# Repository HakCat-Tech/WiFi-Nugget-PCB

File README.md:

# WiFi Nugget PCB
This repository contains the PCB design files for the ESP8266 based WiFi Nugget.

### Change Log + Specs
**Beta-v1.0:**  
This design is a proof of concept for a slimmer, more easily manfacturable design based off surface mount components.   
- 0603 SMD components
- ESP12F based module
- SH1106 OLED Screen
- Minimal PCB art

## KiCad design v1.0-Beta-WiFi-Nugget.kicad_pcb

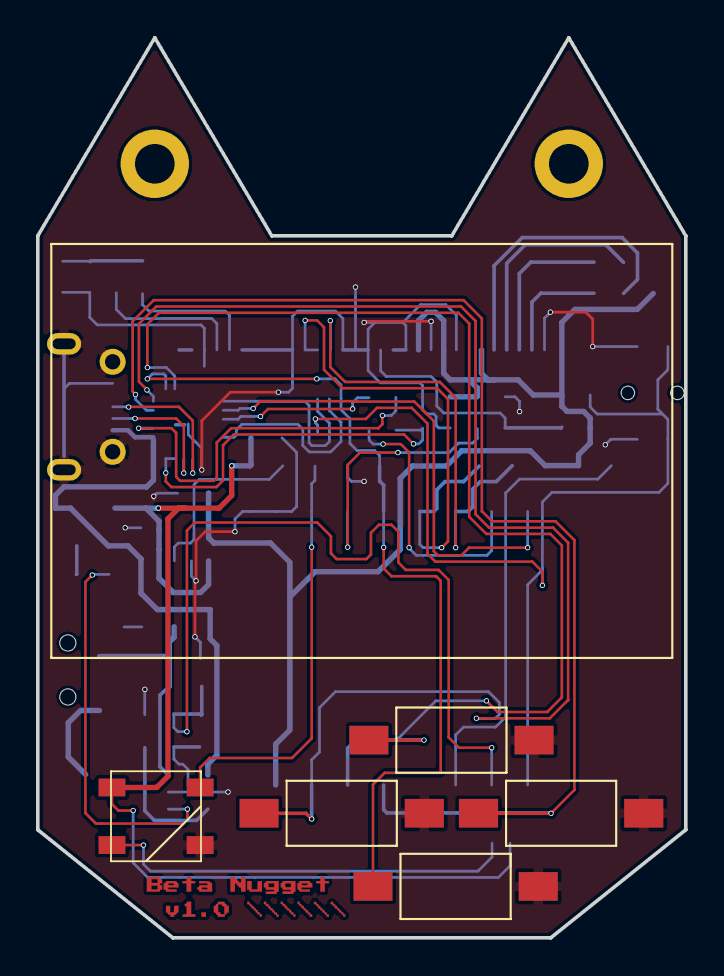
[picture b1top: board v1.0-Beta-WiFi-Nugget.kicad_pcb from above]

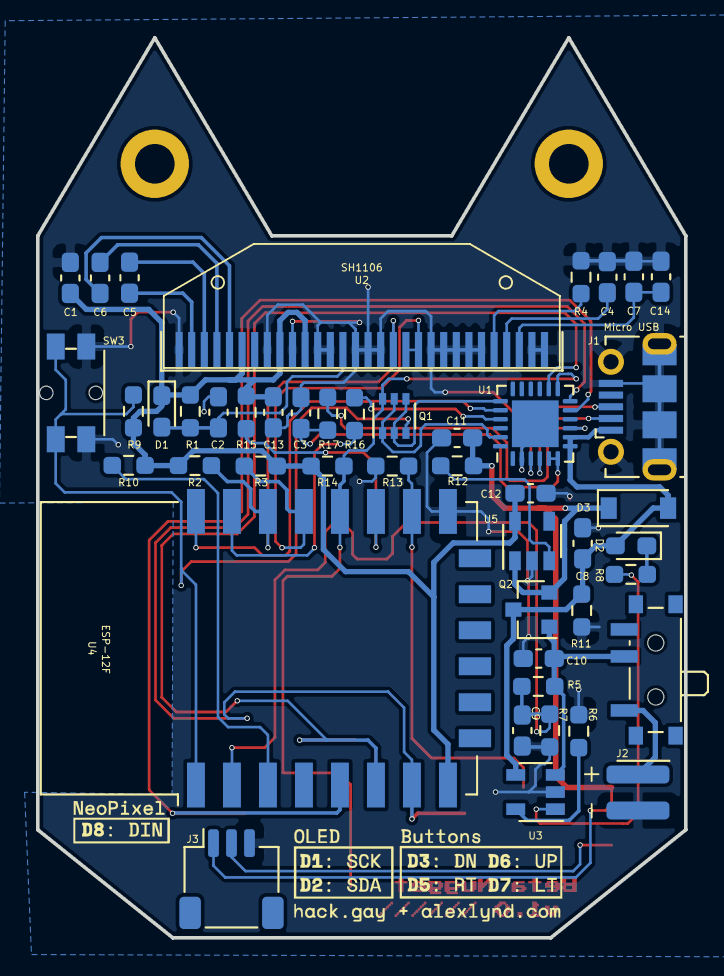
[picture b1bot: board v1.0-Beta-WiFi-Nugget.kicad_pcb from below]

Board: 2 copper layers, 36.0 x 50.0 mm, 52 parts (46 on the bottom side), 39 nets.

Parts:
C1, C3, C5, C6: 1 μF; C_0603_1608Metric_Pad1.08x0.95mm_HandSolder
C2: 10 μF; C_0603_1608Metric_Pad1.08x0.95mm_HandSolder
C4, C8, C10, C11, C12, C13: 4.7μF; C_0603_1608Metric_Pad1.08x0.95mm_HandSolder
C7, C14: C_Small; C_0603_1608Metric_Pad1.08x0.95mm_HandSolder
C9: 1μF; C_0603_1608Metric_Pad1.08x0.95mm_HandSolder
D1: SS14; LED_0603_1608Metric_Pad1.05x0.95mm_HandSolder
D2: RED; LED_0603_1608Metric_Pad1.05x0.95mm_HandSolder
D3: SS14; D_SOD-123
D4: WS2812B; LED_WS2812B_PLCC4_5.0x5.0mm_P3.2mm
J1: Micro USB; USB_Micro-B_Molex-105017-0001
J2: JST PH 2.0; JST_PH_S2B-PH-SM4-TB_1x02-1MP_P2.00mm_Horizontal
J3: JST_SH_SM03B-SRSS-TB_1x03-1MP_P1.00mm_Horizontal
Q1: UMH3N; SOT-363_SC-70-6
Q2: DMG3415; SOT-23
R1, R2, R3, R6, R13: 4.7K; R_0603_1608Metric_Pad0.98x0.95mm_HandSolder
R4: 560K; R_0603_1608Metric_Pad0.98x0.95mm_HandSolder
R5: 100K; R_0603_1608Metric_Pad0.98x0.95mm_HandSolder
R7: 27K; R_0603_1608Metric_Pad0.98x0.95mm_HandSolder
R8: 5K; R_0603_1608Metric_Pad0.98x0.95mm_HandSolder
R9, R10, R11, R12, R14, R15: 10K; R_0603_1608Metric_Pad0.98x0.95mm_HandSolder
R16: 1K; R_0603_1608Metric_Pad0.98x0.95mm_HandSolder
R17: R_Small_US; R_0603_1608Metric_Pad0.98x0.95mm_HandSolder
Ref**: Val**; Deluxe-Nugg-Board-Art
SW1: SPDT; SW_SPDT_PCM12
SW2: UP; SW_SPST_FSMSM
SW3: Reset; Panasonic_EVQPUM_EVQPUD
SW4: DOWN; SW_SPST_FSMSM
SW5: LEFT; SW_SPST_FSMSM
SW6: RIGHT; SW_SPST_FSMSM
U1: CP2102N-A01-GQFN24; QFN-24-1EP_4x4mm_P0.5mm_EP2.6x2.6mm
U2: SH1106; OLED-128O064D
U3: MCP73831-2-OT; SOT-23-5
U4: ESP-12F; ESP-12E
U5: AP2112K-3.3; SOT-23-5

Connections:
+3V3: C1.1, C12.1, C13.1, D1.1, R1.2, R2.1, R3.1, R9.1, R10.1, R14.1, R15.1, U2.6, U2.9, U2.11, U4.8, U5.5
+BATT: C10.1, Q2.1, R5.2, SW1.2, U3.3
A0: C9.2, R5.1, R7.2, U4.2
DOUT: D4.2, J3.2
DTR: Q1.1, Q1.5, U1.23
ESP_RST: Q1.3, R9.2, SW3.1, U4.1
GNDREF: C1.2, C2.2, C3.1, C4.2, C7.1, C8.2, C9.1, C10.2, C11.2, C12.2, C13.2, C14.1, D4.3, J1.5, J1.6, J2.2, J3.3, R4.2, R6.2, R7.1, R11.2, R13.2, SW2.2, SW3.2, SW4.2, SW5.2, SW6.2, U1.2, U1.25, U2.1, U2.8, U2.10, U2.12, U2.13, U2.15, U2.16, U2.17, U2.21, U2.22, U2.23, U2.24, U2.25, U2.29, U2.30, U3.2, U4.15, U5.2
GPIO0: Q1.6, R14.2, SW4.1, U1.13, U4.18
GPIO12: SW2.1, U1.14, U4.6
GPIO13: SW5.1, U1.12, U4.7
GPIO14: SW6.1, U1.11, U4.5
GPIO15: D4.4, R13.1, U4.16
unnamed: C3.2, R17.2, U1.5, U1.6
unnamed: C4.1, U2.27
unnamed: C5.1, U2.2
unnamed: C5.2, U2.3
unnamed: C6.1, U2.4
unnamed: C6.2, U2.5
unnamed: C7.2, C14.2, U2.28
unnamed: D2.1, R8.1
unnamed: J1.2, U1.4
unnamed: J1.3, U1.3
unnamed: J2.1, SW1.1
unnamed: R4.1, U2.26
unnamed: R6.1, U3.5
unnamed: R8.2, U3.1
unnamed: R10.2, U4.3
unnamed: R12.1, U5.3
unnamed: R15.2, U4.17
unnamed: R16.2, U4.21
unnamed: R17.1, U1.9
RES: C2.1, D1.2, R1.1, U2.14
RTS: Q1.2, Q1.4, U1.19
SCL: R2.2, U2.18, U4.20
SDA: R3.2, U2.19, U2.20, U4.19
TXD: U1.20, U4.22
USB_RX: R16.1, U1.21
VBUS: C8.1, D2.2, D3.2, J1.1, Q2.3, R11.1, U1.7, U1.8, U3.4
VMAX: C11.1, D3.1, D4.1, J3.1, Q2.2, R12.2, U5.1

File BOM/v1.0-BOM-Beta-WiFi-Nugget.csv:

Reference, Quantity, Value, Footprint, Datasheet
C4 C8 C10 C11 C12 C13 ,6,4.7μF,Capacitor_SMD:C_0603_1608Metric_Pad1.08x0.95mm_HandSolder,~
C2 ,1,4.7 μF,Capacitor_SMD:C_0603_1608Metric_Pad1.08x0.95mm_HandSolder,~
C1 C3 C5 C6 C7 C14 ,6,1 μF,Capacitor_SMD:C_0603_1608Metric_Pad1.08x0.95mm_HandSolder,~
C9 ,1,1μF,Capacitor_SMD:C_0603_1608Metric_Pad1.08x0.95mm_HandSolder,~
D1 ,1,SS14,LED_SMD:LED_0603_1608Metric_Pad1.05x0.95mm_HandSolder,~
D2 ,1,RED 0603,LED_SMD:LED_0603_1608Metric_Pad1.05x0.95mm_HandSolder,~
D3 ,1,SS14,Diode_SMD:D_SOD-123,~
D4 ,1,WS2812B,LED_SMD:LED_WS2812B_PLCC4_5.0x5.0mm_P3.2mm,https://cdn-shop.adafruit.com/datasheets/WS2812B.pdf
J1 ,1,Micro USB,Connector_USB:USB_Micro-B_Molex-105017-0001,~
J2 ,1,JST PH 2.0,Connector_JST:JST_PH_S2B-PH-SM4-TB_1x02-1MP_P2.00mm_Horizontal,~
J3 ,1,NeoPixel Breakout,Connector_JST:JST_SH_SM03B-SRSS-TB_1x03-1MP_P1.00mm_Horizontal,~
Q1 ,1,UMH3N,Package_TO_SOT_SMD:SOT-363_SC-70-6,http://rohmfs.rohm.com/en/products/databook/datasheet/discre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
Q2 ,1,DMG3415,Package_TO_SOT_SMD:SOT-23,~
R1 R2 R3 R6 R8 R13 R16 R17 ,8,4.7K,Resistor_SMD:R_0603_1608Metric_Pad0.98x0.95mm_HandSolder,~
R9 R10 R11 R12 R14 R15 ,6,10K,Resistor_SMD:R_0603_1608Metric_Pad0.98x0.95mm_HandSolder,~
R4 ,1,560K,Resistor_SMD:R_0603_1608Metric_Pad0.98x0.95mm_HandSolder,~
R5 ,1,100K,Resistor_SMD:R_0603_1608Metric_Pad0.98x0.95mm_HandSolder,~
R7 ,1,27K,Resistor_SMD:R_0603_1608Metric_Pad0.98x0.95mm_HandSolder,~
SW1 ,1,SPDT,Button_Switch_SMD:SW_SPDT_PCM12,https://www.digikey.com/en/products/detail/e-switch/EG1215AA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
SW2 ,1,UP,Button_Switch_SMD:SW_SPST_FSMSM,https://www.digikey.com/en/products/detail/c-k/PTS636-SM25F-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
SW3 ,1,Reset,Button_Switch_SMD:Panasonic_EVQPUM_EVQPUD,https://www.digikey.com/en/products/detail/w%C3%BCrth-elektr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
SW4 ,1,DOWN,Button_Switch_SMD:SW_SPST_FSMSM,https://www.digikey.com/en/products/detail/c-k/PTS636-SM25F-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
SW5 ,1,LEFT,Button_Switch_SMD:SW_SPST_FSMSM,https://www.digikey.com/en/products/detail/c-k/PTS636-SM25F-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
SW6 ,1,RIGHT,Button_Switch_SMD:SW_SPST_FSMSM,https://www.digikey.com/en/products/detail/c-k/PTS636-SM25F-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
U1 ,1,CP2102N-A01-GQFN24,Package_DFN_QFN:QFN-24-1EP_4x4mm_P0.5mm_EP2.6x2.6mm,https://www.silabs.com/documents/public/data-sheets/cp2102n-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
U2 ,1,SH1106,Display:OLED-128O064D,https://www.vishay.com/docs/37902/oled128o064dbpp3n00000.pdf
U3 ,1,MCP73831-2-OT,Package_TO_SOT_SMD:SOT-23-5,http://ww1.microchip.com/downloads/en/DeviceDoc/20001984g.pdf
U4 ,1,ESP-12F,RF_Module:ESP-12E,http://wiki.ai-thinker.com/_media/esp8266/esp8266_series_mod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
U5 ,1,AP2112K-3.3,Package_TO_SOT_SMD:SOT-23-5,https://www.diodes.com/assets/Datasheets/AP2112.pdf

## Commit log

2021-12-03 v1.0 beta PCB files
2021-12-03 v1.0 board file update
2021-12-08 v1.0 gerber + bom files
2021-12-08 update naming convention + board files
2021-12-08 version
2021-12-08 update file names
